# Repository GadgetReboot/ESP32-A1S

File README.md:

# ESP32-A1S
Breakout PCB for the ESP32-A1S module including an audio amp and basic GPIO headers, USB interface  
In Arduino IDE, the ESP32 board to choose is "ESP32 Dev Module"  
Use default configuration settings  
Then Enable PSRAM  <BR><BR>
The USB Micro-B connector on the board is GCT p/n USB3076-30-A   available from Digikey, Mouser etc

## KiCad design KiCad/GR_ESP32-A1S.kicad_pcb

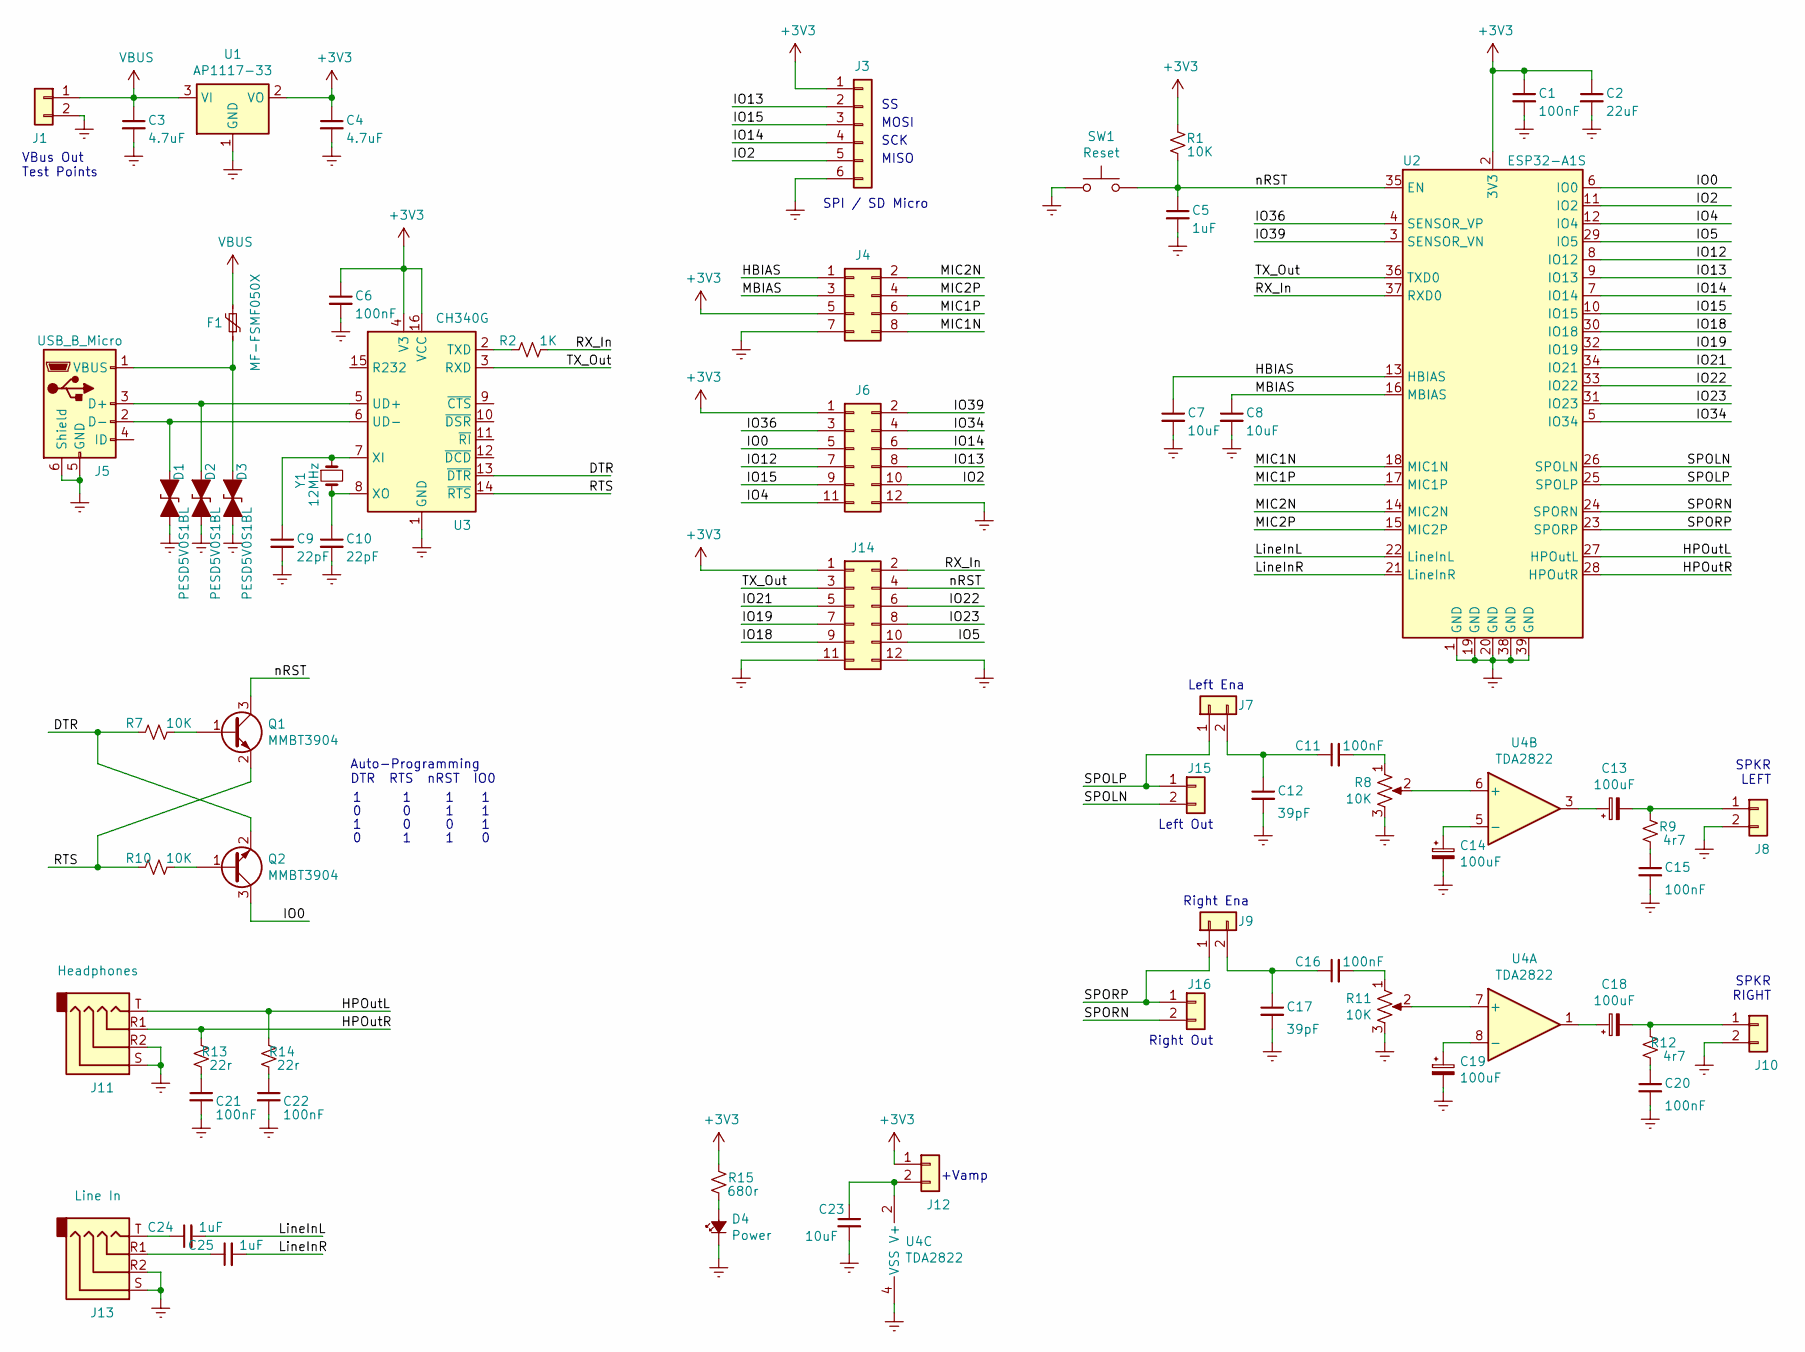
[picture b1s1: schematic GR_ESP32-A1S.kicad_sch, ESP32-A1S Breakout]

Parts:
C1, C6, C11, C15, C16, C20, C21, C22: 100nF; C_0805_2012Metric_Pad1.15x1.40mm_HandSolder
C2: 22uF; C_0805_2012Metric_Pad1.15x1.40mm_HandSolder
C3, C4: 4.7uF; C_0805_2012Metric_Pad1.15x1.40mm_HandSolder
C5, C24, C25: 1uF; C_0805_2012Metric_Pad1.15x1.40mm_HandSolder
C7, C8, C23: 10uF; C_0805_2012Metric_Pad1.15x1.40mm_HandSolder
C9, C10: 22pF; C_0805_2012Metric_Pad1.15x1.40mm_HandSolder
C12, C17: 39pF; C_0805_2012Metric_Pad1.15x1.40mm_HandSolder
C13, C14, C18, C19: 100uF; CP_Radial_D5.0mm_P2.50mm
D1, D2, D3: PESD5V0S1BL; SOD-882
D4: Power; LED_0805_2012Metric_Pad1.15x1.40mm_HandSolder
F1: MF-FSMF050X; R_0603_1608Metric_Pad1.05x0.95mm_HandSolder
J1, J7, J8, J9, J10, J12, J15, J16: Conn_01x02; PinHeader_1x02_P2.54mm_Vertical
J3: SPI; PinHeader_1x06_P2.54mm_Vertical
J4: Conn_02x04_Odd_Even; PinHeader_2x04_P2.54mm_Vertical
J5: USB_B_Micro; USB_Micro-B_GCT_USB3076-30-A
J6, J14: Conn_02x06_Odd_Even; PinHeader_2x06_P2.54mm_Vertical
J11: Headphones; Jack_3.5mm_PJ320D_Horizontal
J13: Line In; Jack_3.5mm_PJ320D_Horizontal
Q1, Q2: MMBT3904; SOT-23
R1, R7, R10: 10K; R_0805_2012Metric_Pad1.15x1.40mm_HandSolder
R2: 1K; R_0805_2012Metric_Pad1.15x1.40mm_HandSolder
R8, R11: 10K; Potentiometer_Vishay_T73YP_Vertical
R9, R12: 4r7; R_0805_2012Metric_Pad1.15x1.40mm_HandSolder
R13, R14: 22r; R_0805_2012Metric_Pad1.15x1.40mm_HandSolder
R15: 680r; R_0805_2012Metric_Pad1.15x1.40mm_HandSolder
SW1: Reset; SW_SPST_FSMSM
U1: AP1117-33; SOT-223-3_TabPin2
U2: ESP32-A1S
U3: CH340G; SOIC-16_3.9x9.9mm_P1.27mm
U4: TDA2822; SOIC-8_3.9x4.9mm_P1.27mm
Y1: 12MHz; Crystal_SMD_HC49-SD_HandSoldering

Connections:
+3V3: C1.1, C2.1, C4.1, C6.1, J3.1, J4.5, J6.1, J12.1, J14.1, R1.1, R15.1, U1.2 (VO), U2.2 (3V3), U3.4 (V3), U3.16 (VCC)
/DTR: Q2.2 (E), R7.1, U3.13 (~DTR)
/HBIAS: C7.1, J4.1, U2.13 (HBIAS)
/HPOutL: J11.T, R14.1, U2.27 (HPOutL)
/HPOutR: J11.R1, R13.1, U2.28 (HPOutR)
/IO0: J6.5, Q2.3 (C), U2.6 (IO0)
/IO2: J3.5, J6.10, U2.11 (IO2)
/IO4: J6.11, U2.12 (IO4)
/IO5: J14.10, U2.29 (IO5)
/IO12: J6.7, U2.8 (IO12)
/IO13: J3.2, J6.8, U2.9 (IO13)
/IO14: J3.4, J6.6, U2.7 (IO14)
/IO15: J3.3, J6.9, U2.10 (IO15)
/IO18: J14.9, U2.30 (IO18)
/IO19: J14.7, U2.32 (IO19)
/IO21: J14.5, U2.34 (IO21)
/IO22: J14.6, U2.33 (IO22)
/IO23: J14.8, U2.31 (IO23)
/IO34: J6.4, U2.5 (IO34)
/IO36: J6.3, U2.4 (SENSOR_VP)
/IO39: J6.2, U2.3 (SENSOR_VN)
/LineInL: C24.2, U2.22 (LineInL)
/LineInR: C25.2, U2.21 (LineInR)
/MBIAS: C8.1, J4.3, U2.16 (MBIAS)
/MIC1N: J4.8, U2.18 (MIC1N)
/MIC1P: J4.6, U2.17 (MIC1P)
/MIC2N: J4.2, U2.14 (MIC2N)
/MIC2P: J4.4, U2.15 (MIC2P)
/RTS: Q1.2 (E), R10.1, U3.14 (~RTS)
/RX_In: J14.2, R2.2, U2.37 (RXD0)
/SPOLN: J15.2, U2.26 (SPOLN)
/SPOLP: J7.1, J15.1, U2.25 (SPOLP)
/SPORN: J16.2, U2.24 (SPORN)
/SPORP: J9.1, J16.1, U2.23 (SPORP)
/TX_Out: J14.3, U2.36 (TXD0), U3.3 (RXD)
/nRST: C5.1, J14.4, Q1.3 (C), R1.2, SW1.2, U2.35 (EN)
GNDREF: C1.2, C2.2, C3.2, C4.2, C5.2, C6.2, C7.2, C8.2, C9.2, C10.2, C12.2, C14.2, C15.2, C17.2, C19.2, C20.2, C21.2, C22.2, C23.2, D1.2 (A2), D2.2 (A2), D3.2 (A2), D4.1 (K), J1.2, J3.6, J4.7, J5.5 (GND), J5.6 (Shield), J6.12, J8.2, J10.2, J11.R2, J11.S, J13.R2, J13.S, J14.11, J14.12, R8.3, R11.3, SW1.1, U1.1 (GND), U2.1 (GND), U2.19 (GND), U2.20 (GND), U2.38 (GND), U2.39 (GND), U3.1 (GND), U4.4 (VSS)
unnamed: C9.1, U3.7 (XI), Y1.1
unnamed: C10.1, U3.8 (XO), Y1.2
unnamed: C11.1, C12.1, J7.2
unnamed: C11.2, R8.1
unnamed: C13.1, U4.3
unnamed: C13.2, J8.1, R9.1
unnamed: C14.1, U4.5 (-)
unnamed: C15.1, R9.2
unnamed: C16.1, C17.1, J9.2
unnamed: C16.2, R11.1
unnamed: C18.1, U4.1
unnamed: C18.2, J10.1, R12.1
unnamed: C19.1, U4.8 (-)
unnamed: C20.1, R12.2
unnamed: C21.1, R13.2
unnamed: C22.1, R14.2
unnamed: C23.1, J12.2, U4.2 (V+)
unnamed: C24.1, J13.T
unnamed: C25.1, J13.R1
unnamed: D1.1 (A1), J5.2 (D-), U3.6 (UD-)
unnamed: D2.1 (A1), J5.3 (D+), U3.5 (UD+)
unnamed: D4.2 (A), R15.2
unnamed: Q1.1 (B), R7.2
unnamed: Q2.1 (B), R10.2
unnamed: R2.1, U3.2 (TXD)
unnamed: R8.2, U4.6 (+)
unnamed: R11.2, U4.7 (+)

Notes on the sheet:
Left Out
1 0 0 1
Right Ena
SPKR RIGHT
SPKR LEFT
SPI / SD Micro
Right Out
+Vamp
MISO
0 0 1 1
1 1 1 1
MOSI
Auto-Programming DTR RTS nRST IO0
Left Ena
SCK
0 1 1 0
VBus Out Test Points

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
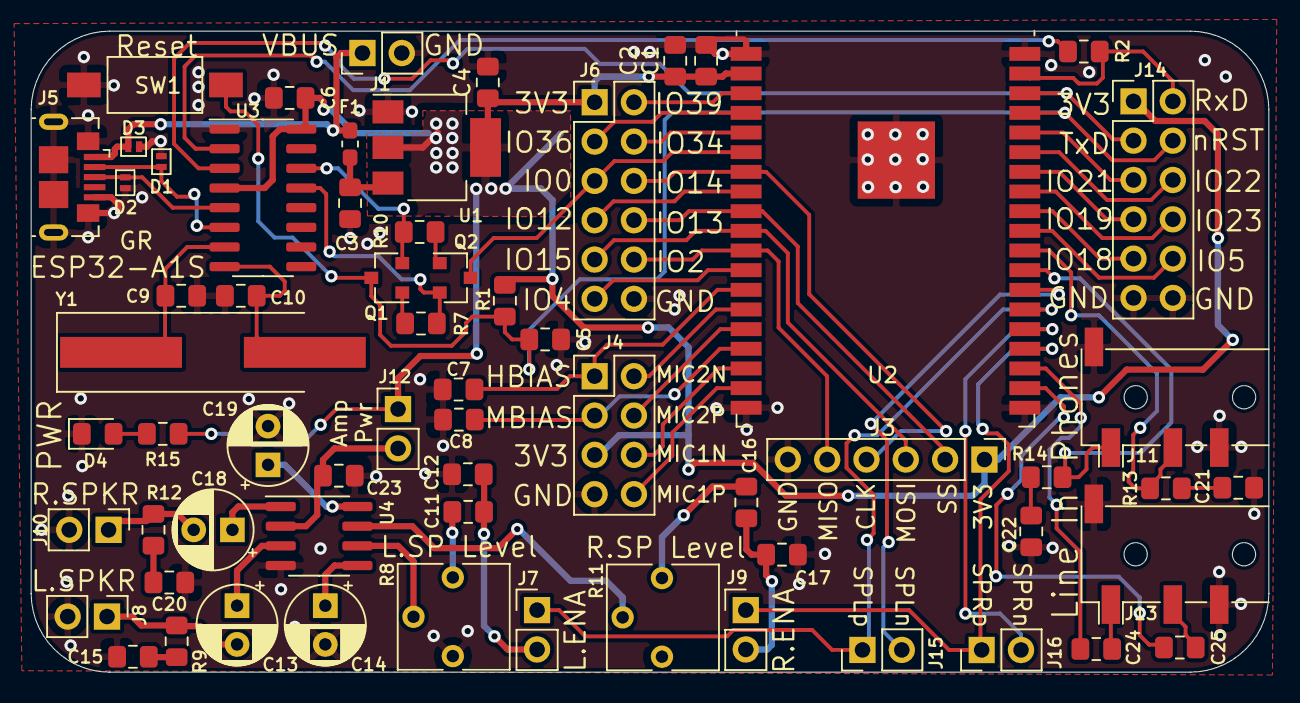
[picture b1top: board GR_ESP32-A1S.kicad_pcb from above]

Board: 2 copper layers, 79.9 x 41.4 mm, 64 parts (0 on the bottom side), 66 nets.

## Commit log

2021-05-11 Rename sketches/TalkingClockI2S.ino to sketches/TalkingClockI2S/TalkingClockI2S.ino
